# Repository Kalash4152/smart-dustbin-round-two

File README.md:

This project was developed as part of DJSCE Unplugged 2.0 – A Hardware Hackathon, where we designed and simulated a Smart Dustbin & Smart Traffic Lights system using Arduino, ESP32, and various sensors. The goal was to integrate IoT and automation to enhance urban infrastructure.

⚙️ Project Features
1️⃣ Smart Dustbin
✔️ Automated Lid Mechanism – Uses an ultrasonic sensor to detect nearby users and open the lid.
✔️ Fill-Level Detection – Monitors the dustbin's capacity using IR sensors and sends real-time data.
✔️ IoT Integration – Uses ESP32 to transmit fill-level data to a cloud server/dashboard.
✔️ Alerts & Optimization – Notifies waste collection teams when bins are full.

2️⃣ Smart Traffic Lights
✔️ Adaptive Signal Control – Uses IR sensors to measure traffic density and adjust light durations accordingly.
✔️ Emergency Vehicle Priority – Detects emergency vehicles via RFID and provides them a green corridor.
✔️ Remote Monitoring – Traffic data is sent to a cloud server for analysis and optimization.

🛠️ Tech Stack & Tools
Microcontrollers: Arduino, ESP32
Sensors: Ultrasonic, IR, RFID
Software & Simulation: Proteus, KiCad, Fusion 360
Programming: C++, Python
Communication: Wi-Fi (ESP32), RFID
🔬 Development Process
📌 Phase 1: Idea & System Architecture
Designed a detailed system architecture to ensure feasibility.
Simulated the circuit using Proteus before hardware implementation.
📌 Phase 2: PCB Design Challenge
Created PCB schematics and layouts using KiCad & Fusion 360 within a 4-hour challenge.
Worked on component placement, routing, and optimization.
📈 Results & Achievements
✅ Shortlisted in the Top 40 teams out of numerous entries.
✅ Recognized as the only first-year team to compete at this level.
✅ Gained valuable experience in embedded systems, IoT, and PCB design.

🎯 Future Improvements
🔹 Optimize power consumption for better efficiency.
🔹 Enhance cloud integration for real-time monitoring and analytics.
🔹 Deploy ML models for predictive waste management & traffic optimization

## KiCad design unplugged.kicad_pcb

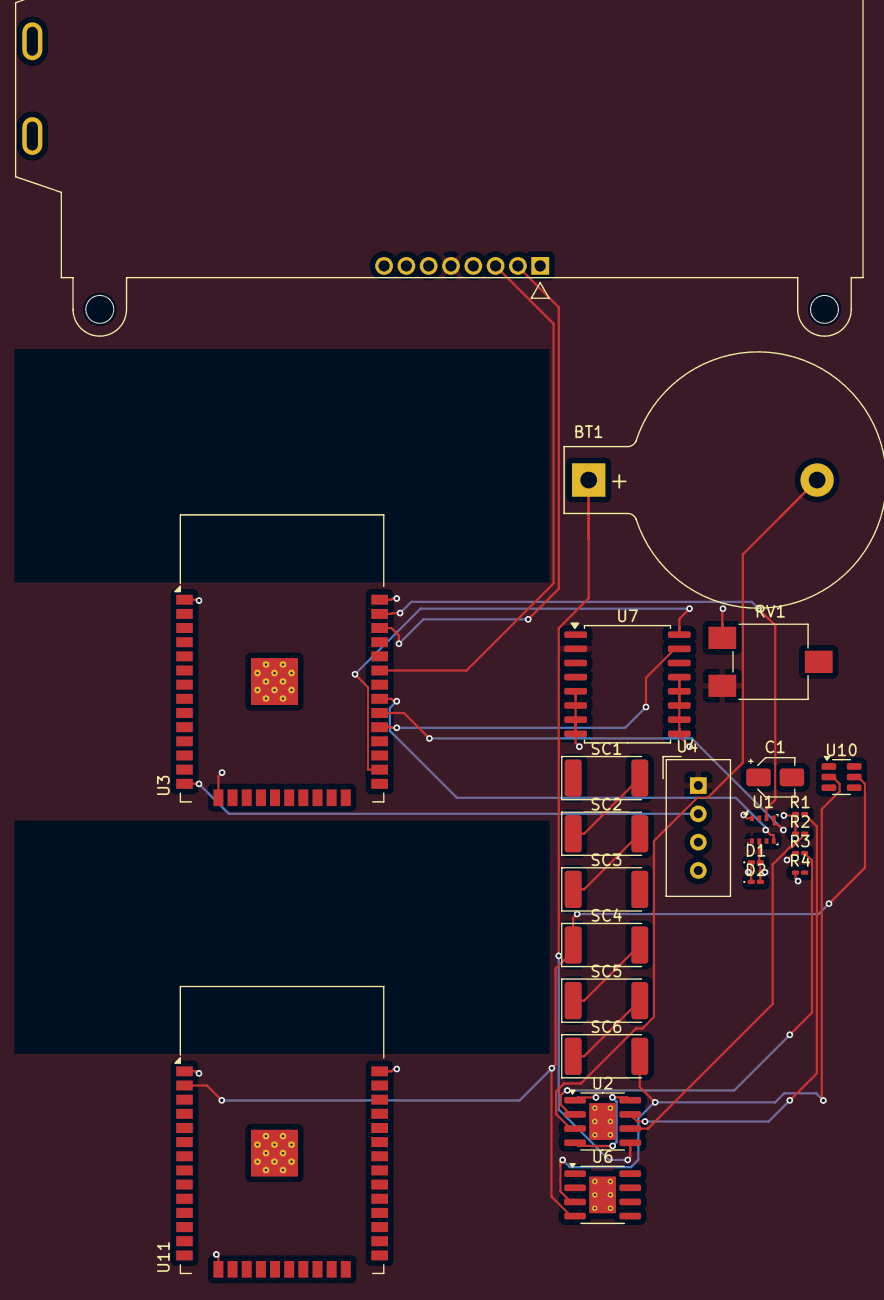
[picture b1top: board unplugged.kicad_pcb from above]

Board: 2 copper layers, 24 parts (0 on the bottom side), 22 nets.

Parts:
BT1: Battery; BatteryHolder_Keystone_103_1x20mm
C1: C; CP_Elec_3x5.4
D1, D2: LED; LED_0201_0603Metric_Pad0.64x0.40mm_HandSolder
R1, R2, R3: 1K; R_0201_0603Metric_Pad0.64x0.40mm_HandSolder
R4: 10K; R_0201_0603Metric_Pad0.64x0.40mm_HandSolder
RV1: POT; Potentiometer_ACP_CA6-VSMD_Vertical
SC1, SC2, SC3, SC4, SC5, SC6: 2V; D_2512_6332Metric_Pad1.52x3.35mm_HandSolder
U1: BME280; Bosch_LGA-8_2.5x2.5mm_P0.65mm_ClockwisePinNumbering
U2, U6: TP4056-42-ESOP8; SOIC-8-1EP_3.9x4.9mm_P1.27mm_EP2.41x3.3mm_ThermalVias
U3, U11: ESP32-WROOM-32
U4: DHT11; Aosong_DHT11_5.5x12.0_P2.54mm
U7: DS3231M; SOIC-16W_7.5x10.3mm_P1.27mm
U9: OLED; NHD-C0220BiZ
U10: MT3608; SOT-23-6

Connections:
+5V: RV1.1, U1.8 (VDD), U4.1 (VDD), U7.2 (VCC), U9.5 (VDD)
GND: D1.1 (K), D1.2 (A), D2.1 (K), D2.2 (A), R1.1, R2.1, R3.1, R4.1, RV1.3, U1.1 (GND), U1.7 (GND), U2.1 (TEMP), U3.1 (GND), U3.15 (GND), U3.38 (GND), U3.39 (GND), U4.4 (GND), U7.5 (GND), U7.6 (GND), U7.7 (GND), U7.8 (GND), U7.9 (GND), U7.10 (GND), U7.11 (GND), U7.12 (GND), U7.13 (GND), U9.4 (VSS), U11.1 (GND), U11.15 (GND), U11.38 (GND), U11.39 (GND)
unnamed: BT1.1 (+), U2.5 (BAT)
unnamed: BT1.2 (-), U2.3 (GND)
unnamed: SC1.2 (-), SC2.1 (+)
unnamed: SC2.2 (-), SC3.1 (+)
unnamed: SC4.1 (+), U6.4 (V_{CC}), U10.5 (IN), U11.2 (VDD)
unnamed: SC4.2 (-), SC5.1 (+)
unnamed: SC5.2 (-), SC6.1 (+)
unnamed: SC6.2 (-), U6.3 (GND), U10.2 (GND)
unnamed: U1.4 (SCK), U3.30 (IO18)
unnamed: U1.3 (SDI), U3.37 (IO23)
unnamed: U1.5 (SDO), U3.31 (IO19)
unnamed: U2.4 (V_{CC}), U2.8 (CE)
unnamed: R3.2, U2.2 (PROG)
unnamed: R1.2, U2.7 (~CHRG)
unnamed: R2.2, U2.6 (~STDBY)
unnamed: U3.26 (IO4), U7.16 (SCL)
unnamed: U3.29 (IO5), U7.15 (SDA)
unnamed: U3.14 (IO12), U4.2 (DATA)
unnamed: U3.33 (IO21), U9.3 (SDA)
unnamed: U3.36 (IO22), U9.2 (SCL)
